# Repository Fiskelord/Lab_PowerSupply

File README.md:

# Lab_Supply
Switch mode power supply, intended as a lab power supply.<br />
The power supply will be made with a custom Fairchild power module, so unfortunately no datasheet available, but if you want to know more about the module, ask me and we will see if i am allowed to share the information or not.<br />
The project is made with KiCAD, and the libraries are included and imported in the "right way", so you should be able to simply open the project and view/edit it after download.

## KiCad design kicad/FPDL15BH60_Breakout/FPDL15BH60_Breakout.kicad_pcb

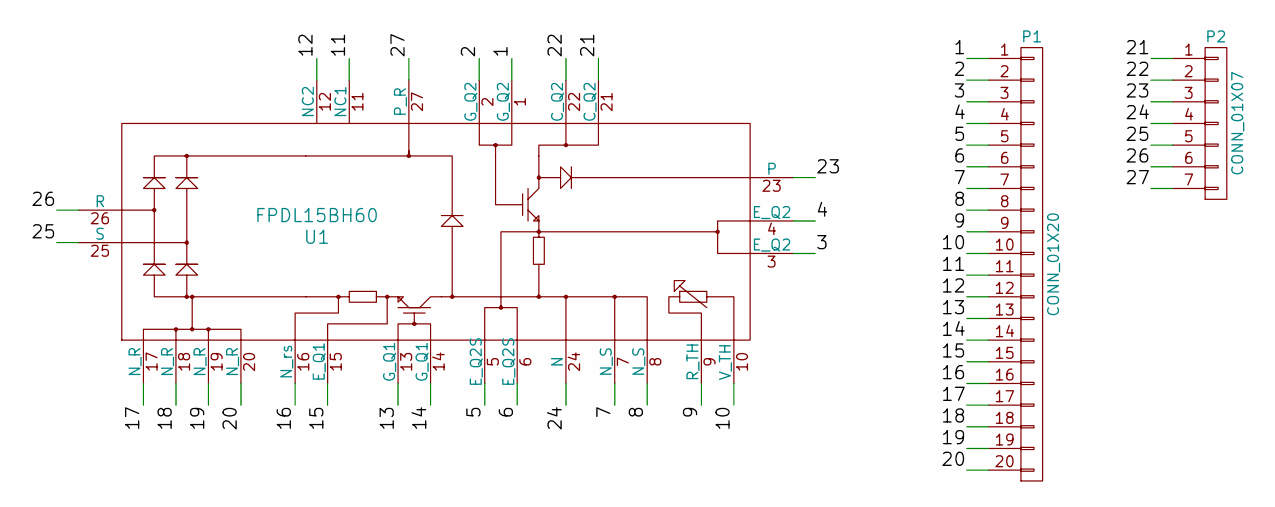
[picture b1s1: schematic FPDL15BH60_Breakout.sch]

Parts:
P1: CONN_01X20; Pin_Header_Straight_1x20_Pitch2.54mm
P2: CONN_01X07; Pin_Header_Straight_1x07_Pitch2.54mm
U1: FPDL15BH60

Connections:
/1: P1.1, U1.1 (G_Q2)
/2: P1.2, U1.2 (G_Q2)
/3: P1.3, U1.3 (E_Q2)
/4: P1.4, U1.4 (E_Q2)
/5: P1.5, U1.5 (E_Q2S)
/6: P1.6, U1.6 (E_Q2S)
/7: P1.7, U1.7 (N_S)
/8: P1.8, U1.8 (N_S)
/9: P1.9, U1.9 (R_TH)
/10: P1.10, U1.10 (V_TH)
/11: P1.11, U1.11 (NC1)
/12: P1.12, U1.12 (NC2)
/13: P1.13, U1.13 (G_Q1)
/14: P1.14, U1.14 (G_Q1)
/15: P1.15, U1.15 (E_Q1)
/16: P1.16, U1.16 (N_rs)
/17: P1.17, U1.17 (N_R)
/18: P1.18, U1.18 (N_R)
/19: P1.19, U1.19 (N_R)
/20: P1.20, U1.20 (N_R)
/21: P2.1, U1.21 (C_Q2)
/22: P2.2, U1.22 (C_Q2)
/23: P2.3, U1.23
/24: P2.4, U1.24 (N)
/25: P2.5, U1.25 (S)
/26: P2.6, U1.26 (R)
/27: P2.7, U1.27 (P_R)

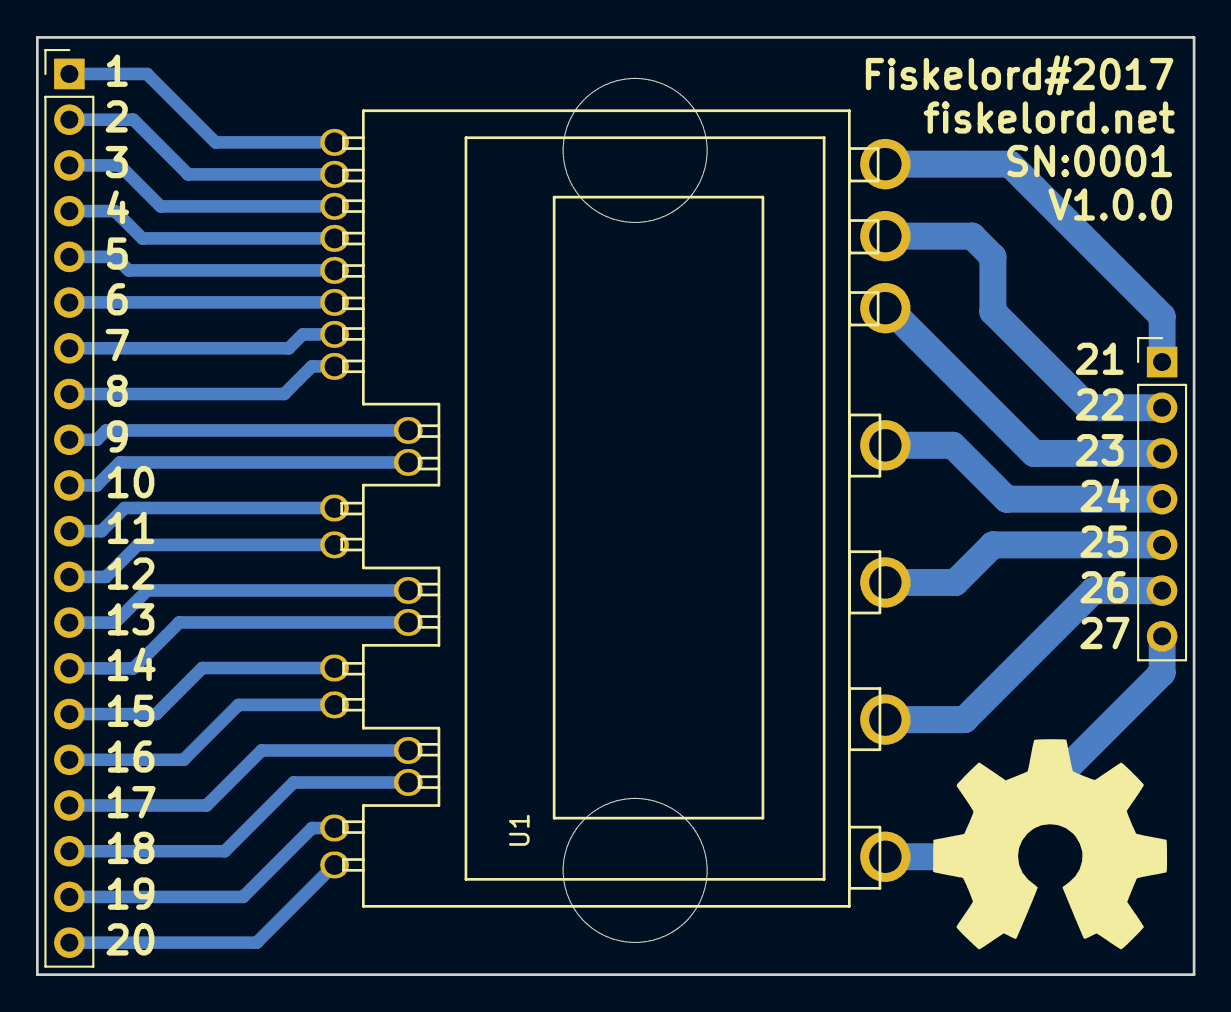
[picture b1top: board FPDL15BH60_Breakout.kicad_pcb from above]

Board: 2 copper layers, 64.3 x 52.1 mm, 3 parts (0 on the bottom side), 27 nets.

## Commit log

2017-08-25 Derpi
2017-08-28 Update on electronic, reorder folder structure
2017-09-10 Moved README and LICENSE
2017-09-12 Made breakout board for power module
2017-10-06 Made OSHW logo
